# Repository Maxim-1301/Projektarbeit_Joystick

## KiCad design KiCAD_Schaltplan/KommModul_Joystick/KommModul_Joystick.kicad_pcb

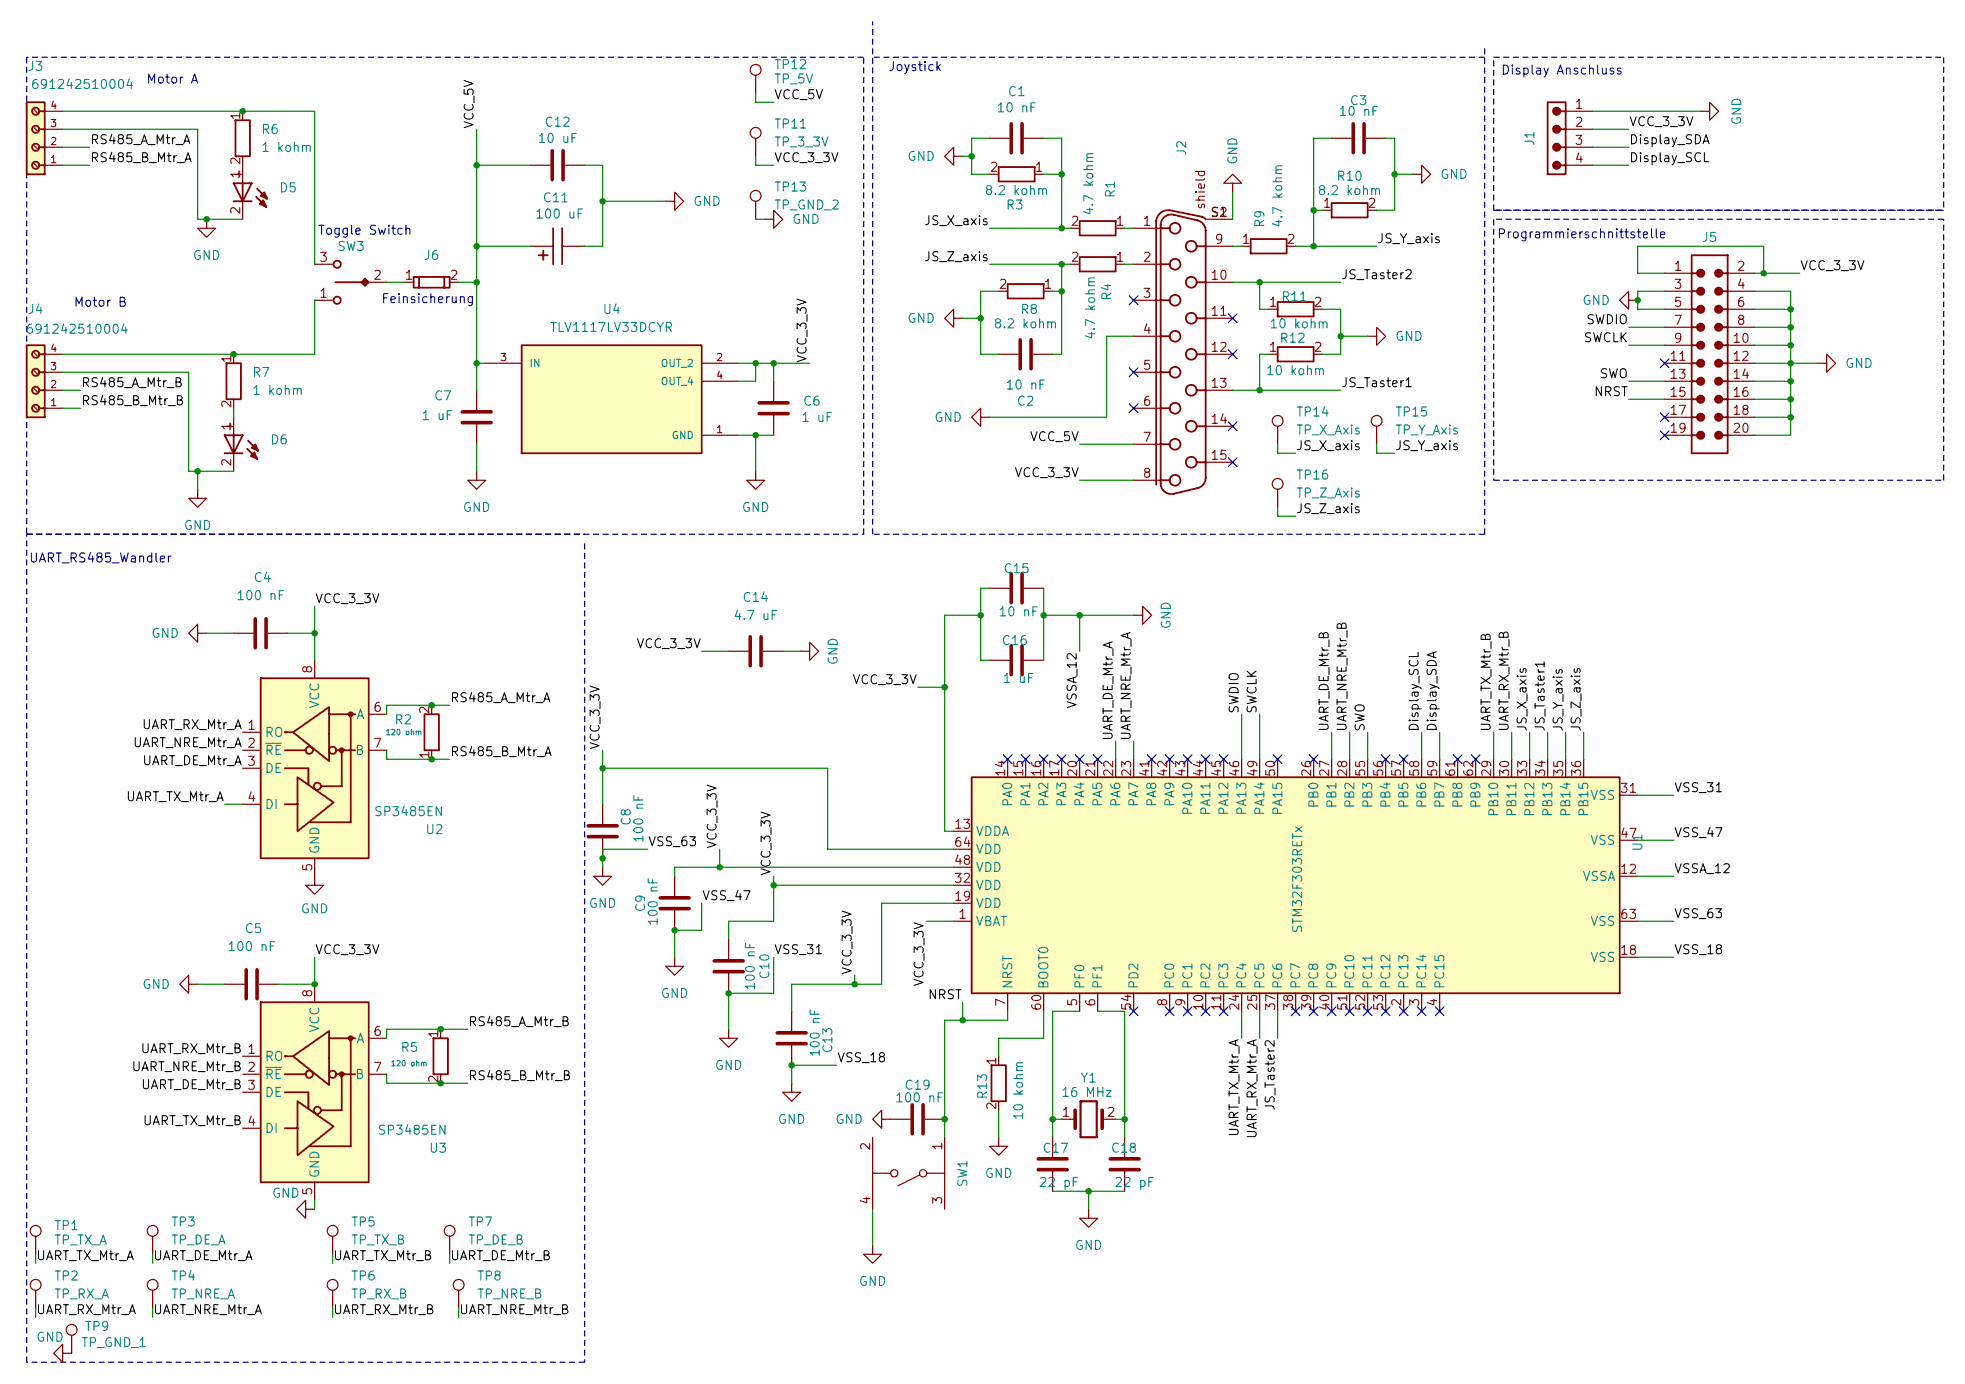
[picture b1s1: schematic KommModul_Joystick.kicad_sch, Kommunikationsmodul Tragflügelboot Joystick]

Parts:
C1, C2, C3, C15: 10 nF; C_Wurth_WCAP-CSGP-1206_H0.8; Voltage 16.0; Part Number 885012208026
C4, C5: 100 nF; C_Wurth_WCAP-CSGP-0805_H0.8_R; Voltage 25.0; Part Number 885012207072
C6, C7, C16: 1 uF; C_Wurth_WCAP-CSGP-1206_H1.15; Voltage 16.0; Part Number 885012208036
C8, C9, C10, C13, C19: 100 nF; C_Wurth_WCAP-CSGP-1206_H0.8; Voltage 16.0; Part Number 885012208030
C11: 100 uF; CP_Wurth_WCAP-PT5H-P2.5D6.3L11_new; Voltage 16.0; Part Number 870235373001
C12: 10 uF; C_Wurth_WCAP-CSGP-1206_H1.6; Voltage 16.0; Part Number 885012208041
C14: 4.7 uF; C_Wurth_WCAP-CSGP-1206_H1.6; Voltage 16.0; Part Number 885012208040
C17, C18: 22 pF; C_Wurth_WCAP-CSGP-1206_H0.8; Voltage 16.0; Part Number 885012008011
D5, D6: 5mmWOS_151051RS11000; D_Wurth_WL-TMRC-5mmWOS_new; Part Number 151051RS11000
J1: 66100411622; J_Wurth_WR-WTB_66100411622_new; Working Voltage (V (AC)) 50
J2: 618015231121; J_Wurth_WR-DSUB_618015231121; Working Voltage (V (AC)) 125
J3, J4: 691242510004; 691242510004_new
J5: 612020235121; J_Wurth_WR-BHD_612020235121; Working Voltage (V (AC)) 250
J6: 696106003002; J_Wurth_WR-FSH_696106003002; Part Number 696106003002
R1, R4, R9: 4.7 kohm; R_Wurth_WRIS-RSKS-1206_R; Part Number 560112132020
R2, R5: 120 ohm; R_Wurth_WRIS-RSKS-1210_R; Part Number 560112140009
R3, R8, R10: 8.2 kohm; R_Wurth_WRIS-RSKS-1206_R; Part Number 560112132051
R6, R7: 1 kohm; R_Wurth_WRIS-RSKS-1206_R; Part Number 560112132038
R11, R12, R13: 10 kohm; R_Wurth_WRIS-RSKS-1206_R; Part Number 560112132018
SW1: 430182080816; SW_Wurth_WS-TASV_430182080816; Part Number 430182080816
SW3: 472123010111; SW_Wurth_WS-TOTV_472123010111; Part Number 472123010111
TP1: TP_TX_A; TestPoint_Pad_D2.0mm
TP2: TP_RX_A; TestPoint_Pad_D2.0mm
TP3: TP_DE_A; TestPoint_Pad_D2.0mm
TP4: TP_NRE_A; TestPoint_Pad_D2.0mm
TP5: TP_TX_B; TestPoint_Pad_D2.0mm
TP6: TP_RX_B; TestPoint_Pad_D2.0mm
TP7: TP_DE_B; TestPoint_Pad_D2.0mm
TP8: TP_NRE_B; TestPoint_Pad_D2.0mm
TP9: TP_GND_1; TestPoint_Pad_D2.0mm
TP11: TP_3_3V; TestPoint_Pad_D2.0mm
TP12: TP_5V; TestPoint_Pad_D2.0mm
TP13: TP_GND_2; TestPoint_Pad_D2.0mm
TP14: TP_X_Axis; TestPoint_Pad_D2.0mm
TP15: TP_Y_Axis; TestPoint_Pad_D2.0mm
TP16: TP_Z_Axis; TestPoint_Pad_D2.0mm
U1: STM32F303RETx; LQFP-64_10x10mm_P0.5mm
U2, U3: SP3485EN; SOIC-8_3.9x4.9mm_P1.27mm
U4: TLV1117LV33DCYR; VREG_TLV1117LV33DCYR_new; PARTREV B
Y1: 16 MHz; Y_Wurth_WE-XTAL_Quartz-HC49-4H_new; Part Number 830058383B

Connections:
/Display_SCL: J1.4, U1.58 (PB6)
/Display_SDA: J1.3, U1.59 (PB7)
/JS_Taster1: J2.13, R12.1, U1.34 (PB13)
/JS_Taster2: J2.10, R11.1, U1.37 (PC6)
/JS_X_axis: C1.1, R1.2, R3.1, TP14.1 (1_1), U1.33 (PB12)
/JS_Y_axis: C3.1, R9.2, R10.1, TP15.1 (1_1), U1.35 (PB14)
/JS_Z_axis: C2.2, R4.2, R8.1, TP16.1 (1_1), U1.36 (PB15)
/NRST: C19.1, J5.15, SW1.1, U1.7 (NRST)
/RS485_A_Mtr_A: J3.2, R2.2, U2.6 (A)
/RS485_A_Mtr_B: J4.2, R5.1, U3.6 (A)
/RS485_B_Mtr_A: J3.1, R2.1, U2.7 (B)
/RS485_B_Mtr_B: J4.1, R5.2, U3.7 (B)
/SWCLK: J5.9, U1.49 (PA14)
/SWDIO: J5.7, U1.46 (PA13)
/SWO: J5.13, U1.55 (PB3)
/UART_DE_Mtr_A: TP3.1 (1_1), U1.22 (PA6), U2.3 (DE)
/UART_DE_Mtr_B: TP7.1 (1_1), U1.27 (PB1), U3.3 (DE)
/UART_NRE_Mtr_A: TP4.1 (1_1), U1.23 (PA7), U2.2 (~RE)
/UART_NRE_Mtr_B: TP8.1 (1_1), U1.28 (PB2), U3.2 (~RE)
/UART_RX_Mtr_A: TP2.1 (1_1), U1.25 (PC5), U2.1 (RO)
/UART_RX_Mtr_B: TP6.1 (1_1), U1.30 (PB11), U3.1 (RO)
/UART_TX_Mtr_A: TP1.1 (1_1), U1.24 (PC4), U2.4 (DI)
/UART_TX_Mtr_B: TP5.1 (1_1), U1.29 (PB10), U3.4 (DI)
/VCC_3_3V: C4.2, C5.2, C6.1, C8.2, C9.1, C10.2, C13.2, C14.1, C15.1, C16.2, J1.2, J2.8, J5.1, J5.2, TP11.1 (1_1), U1.1 (VBAT), U1.13 (VDDA), U1.19 (VDD), U1.32 (VDD), U1.48 (VDD), U1.64 (VDD), U2.8 (VCC), U3.8 (VCC), U4.2 (OUT_2), U4.4 (OUT_4)
/VCC_5V: C7.1, C11.1, C12.2, J2.7, J6.2, TP12.1 (1_1), U4.3 (IN)
GND: C1.2, C2.1, C3.2, C4.1, C5.1, C6.2, C7.2, C8.1, C9.2, C10.1, C11.2, C12.1, C13.1, C14.2, C15.2, C16.1, C17.2, C18.2, C19.2, D5.2 (-), D6.2 (-), J1.1, J2.4, J2.S1 (SHIELD), J2.S2 (SHIELD), J3.3, J4.3, J5.3, J5.4, J5.5, J5.6, J5.8, J5.10, J5.12, J5.14, J5.16, J5.18, J5.20, R3.2, R8.2, R10.2, R11.2, R12.2, R13.2, SW1.4, TP9.1 (1_1), TP13.1 (1_1), U1.12 (VSSA), U1.18 (VSS), U1.31 (VSS), U1.47 (VSS), U1.63 (VSS), U2.5 (GND), U3.5 (GND), U4.1 (GND)
unnamed: D5.1 (+), R6.2
unnamed: D6.1 (+), R7.2
unnamed: J2.1, R1.1
unnamed: J2.2, R4.1
unnamed: J2.9, R9.1
unnamed: J3.4, R6.1, SW3.3
unnamed: J4.4, R7.1, SW3.1
unnamed: J6.1, SW3.2
unnamed: R13.1, U1.60 (BOOT0)
unnamed: C17.1, U1.5 (PF0), Y1.1
unnamed: C18.1, U1.6 (PF1), Y1.2

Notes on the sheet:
Display Anschluss
UART_RS485_Wandler
Feinsicherung
Motor B
Motor A
Programmierschnittstelle
Joystick
Toggle Switch

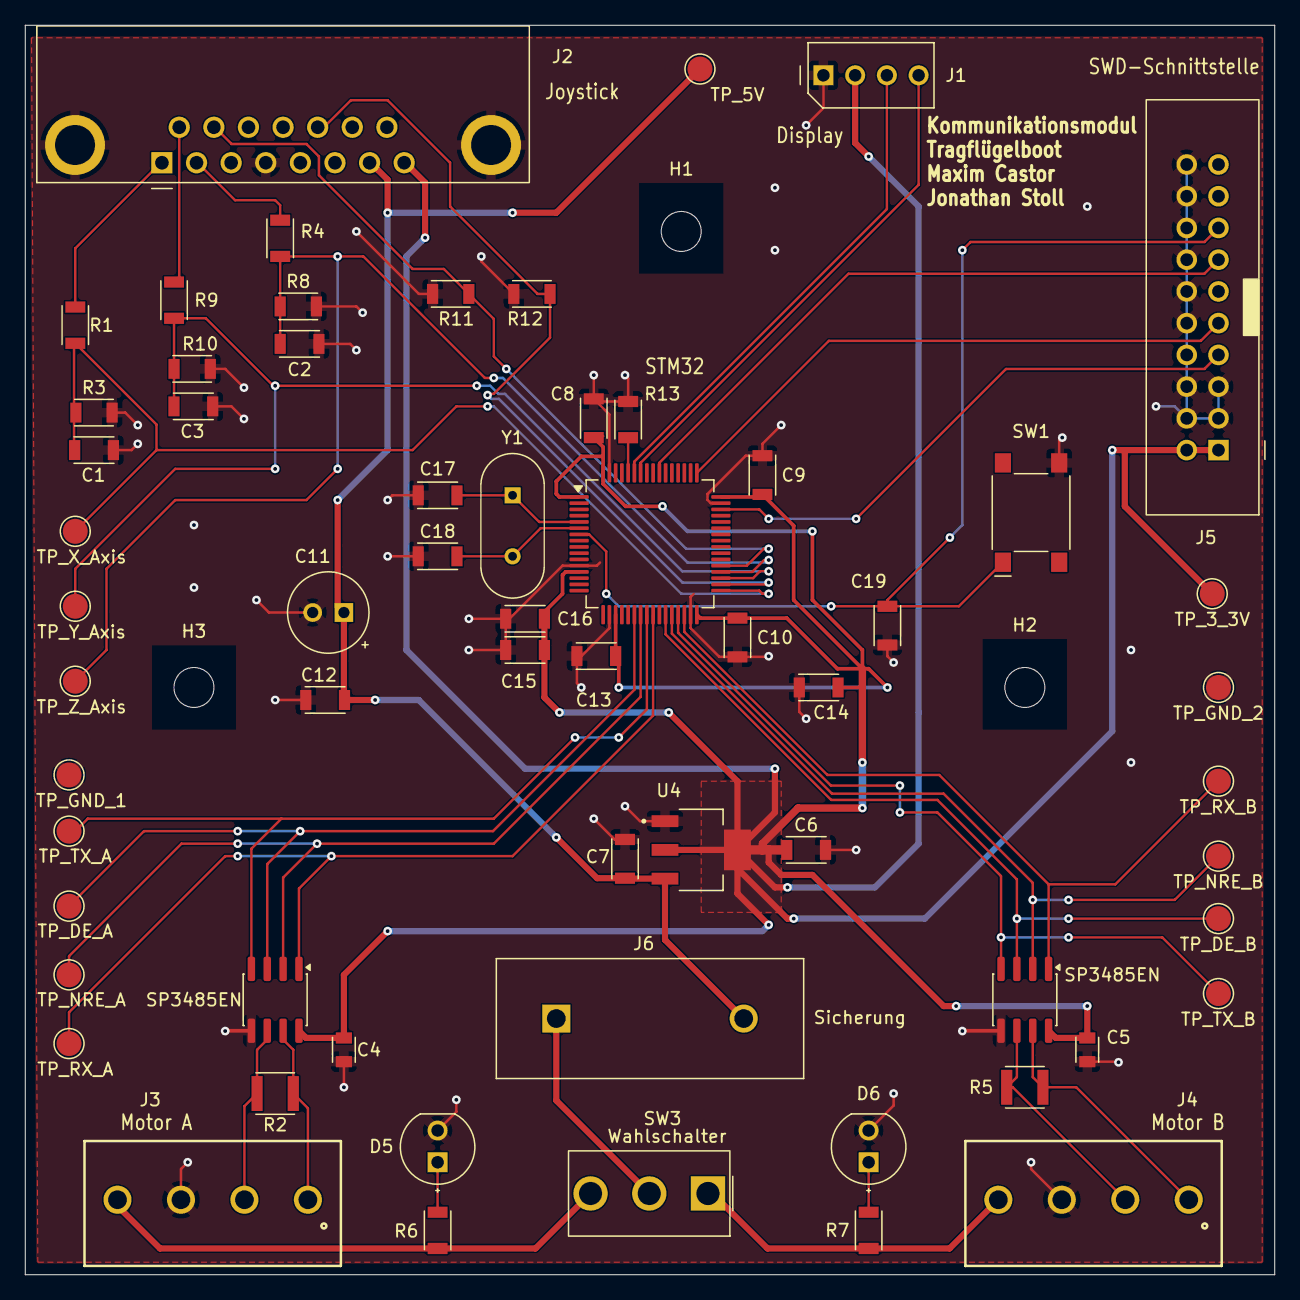
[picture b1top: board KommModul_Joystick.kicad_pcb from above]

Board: 2 copper layers, 100.0 x 100.0 mm, 65 parts (0 on the bottom side), 37 nets.

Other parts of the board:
H1, H2, H3: MountingHole; MountingHole_3.2mm_M3

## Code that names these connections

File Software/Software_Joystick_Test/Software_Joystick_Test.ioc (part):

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Mcu.Name=STM32F303R(D-E)Tx
Mcu.Package=LQFP64
Mcu.UserName=STM32F303RETx
PA13.Mode=Serial_Wire
PA13.Signal=SYS_JTMS-SWDIO
PA14.Mode=Serial_Wire
PA14.Signal=SYS_JTCK-SWCLK
PA6.GPIOParameters=GPIO_Label
PA6.GPIO_Label=MotorA_DE
PA6.Signal=GPIO_Output
PA7.GPIOParameters=GPIO_Label
PA7.GPIO_Label=MotorA_NRE
PA7.Signal=GPIO_Output
PB1.GPIOParameters=GPIO_Label
PB1.GPIO_Label=MotorB_DE
PB1.Signal=GPIO_Output
PB10.GPIOParameters=GPIO_Label
PB10.GPIO_Label=MotorB_UART_TX
PB10.Mode=Asynchronous
PB10.Signal=USART3_TX
PB11.GPIOParameters=GPIO_Label
PB11.GPIO_Label=MotorB_UART_RX
PB11.Mode=Asynchronous
PB11.Signal=USART3_RX
PB12.GPIOParameters=GPIO_Label
PB12.GPIO_Label=Joystick_ADC_X
PB12.Mode=IN3-Single-Ended
PB12.Signal=ADC4_IN3
PB13.GPIOParameters=GPIO_PuPd,GPIO_Label
PB13.GPIO_Label=Joystick_Taster1
PB13.GPIO_PuPd=GPIO_PULLUP
PB13.Signal=GPIO_Input
PB14.GPIOParameters=GPIO_Label
PB14.GPIO_Label=Joystick_ADC_Y
PB14.Mode=IN4-Single-Ended
PB14.Signal=ADC4_IN4
PB15.GPIOParameters=GPIO_Label
PB15.GPIO_Label=Joystick_ADC_Z
PB15.Mode=IN5-Single-Ended
PB15.Signal=ADC4_IN5
PB2.GPIOParameters=GPIO_Label
PB2.GPIO_Label=MotorB_NRE
PB2.Signal=GPIO_Output
PB6.Mode=I2C
PB6.Signal=I2C1_SCL
PB7.Mode=I2C
PB7.Signal=I2C1_SDA
PC4.GPIOParameters=GPIO_Label
PC4.GPIO_Label=MotorA_UART_TX
PC4.Mode=Asynchronous
PC4.Signal=USART1_TX
PC5.GPIOParameters=GPIO_Label
PC5.GPIO_Label=MotorA_UART_RX
PC5.Mode=Asynchronous
PC5.Signal=USART1_RX
PC6.GPIOParameters=GPIO_PuPd,GPIO_Label
PC6.GPIO_Label=Joystick_Taster2
PC6.GPIO_PuPd=GPIO_PULLUP
PC6.Signal=GPIO_Input
PF0-OSC_IN.Mode=HSE-External-Oscillator
PF0-OSC_IN.Signal=RCC_OSC_IN
PF1-OSC_OUT.Mode=HSE-External-Oscillator
PF1-OSC_OUT.Signal=RCC_OSC_OUT
RCC.HSE_VALUE=16000000
RCC.SYSCLKFreq_VALUE=64000000
RCC.SYSCLKSourceVirtual=RCC_SYSCLKSOURCE_PLLCLK
board=custom

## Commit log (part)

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2026-06-11 added files
2026-06-11 Hinzufügen Library
2026-06-26 Commit Schaltplan updates
